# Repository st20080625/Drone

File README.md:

# 自作ドローン

## 概要
このプロジェクトは、自作ドローンの設計・製作・制御を目的としています。各種パーツの選定、組み立て、プログラムによる制御方法についてまとめています。

---

## 📝 目次

* [特徴](#-特徴)
* [外観](#-外観)
* [飛行映像](#-飛行映像)
* [操作方法](#-操作方法)
* [ハード構成](#-ハード構成)
* [インストール](#-インストール)
* [ディレクトリ構成](#-ディレクトリ構成)
* [使い方](#-使い方)
* [参考文献](#-参考文献)

---

## ✨ 特徴

* 自作のドローンファームウェア
* 拡張可能なハードウェア構成

---
## 📷️ 外観

---

## 📹️ 飛行映像
https://github.com/user-attachments/assets/ef20d2a3-a51d-4bfe-b37a-9de0bfae4551

---

## 🎮️ 操作方法
PlayStation5のコントローラを使用して飛ばすことができます。  
左スティックの上下で上昇、降下、右スティックの前後左右で前進、後退、左右移動ができます。  
R,Lボタンで向きを変更できます。  
バツボタンでセンサのキャリブレーションを行い、丸ボタンでモータの回転のオンオフができます。

---

## 🤖 ハード構成
* 制御マイコン: ESP32-WROOM-32D
* コントローラー: PlayStation5 DualSense--

* フレーム: DJI F450
* モーター: BLDC 2212 920kv * 4
* ESC: 20A (最大30A 10秒) * 4
* プロペラ: 10✕4.5 inch * 4
* バッテリー: 4S lipo 5000mAh 100C (3S lipo 2250mAh 60C程度なら満充電で1分程度飛行可能)
* ランディングギア: F450対応のもの
* LEDテープ: SK6812 * 21 (neopixel対応のものなら可) 
### 拡張用
* RaspberryPi4 4GB(RaspberryPi5 8GBはモバイルバッテリー運用は厳しい)
* モバイルバッテリー: 5V3A出力できるものなら可
* 2d lidar: rplidar a1m8

--- 
## 📦 インストール

```bash
# リポジトリをクローン
git clone https://github.com/st20080625/Drone.git

# ディレクトリに移動
cd Drone
```

---

## 📁 ディレクトリ構成

```
Drone/
├── README.md
├── images
├── include                     # ESP32フライトコントローラ用のヘッダ
├── lib                         # ps5コントローラを使うためのライブラリ
├── models                      # 3dプリンタで印刷するようのデータ
├── pcb                         # 回路図,基盤データ
├── platformio.ini              # build定義
├── recv_imu_test               # データ送信テスト
├── slam_raspi                  # マップを作るためのraspi用の環境
├── src                         # ESP32フライトコントローラの実装
```
---

## 🚀 使い方

```bash
# まずはじめにplatformioをインストールします。
pip install platformio

# 次に、src/main.cppのps5.begin(~)の~を使用するコントローラーのmacアドレスに書き換えてください。

# 次にesp32をパソコンに接続し,以下のコマンドを入力します。
# これはプロジェクトのルートディレクトリで行ってください。
platformio run --target upload

# buildとesp32に書き込みが行われます。
```

ドローンの組み立て手順や仕組みを記載します。 

ドローンの飛行を制御するには制御を行うための基盤が必要です。
kicadを使用してpcb/の中にあるdrone.kicad_proを開いて回路図とpcbを確認してください。ガーバーファイルとドリルファイルを出力し、JLCPCBなどにデータを送り、印刷してもらうか,自分でユニバーサル基板に実装するなどをして作成してください。既存ボードを刺す形式なので、使用する基盤とピン配置があっているかを確認して、異なっていれば修正してください。
基盤を固定するためにmodels/の中にあるlidar_mount.stl(追加予定)を印刷し、pcbと固定してください。
その後、f450フレームの上部プレートにネジでmount経由で固定してください。ダブルナットにすれば緩みにくくなると思います。
基盤を作成するとこのようになると思います。

これはバージョンが古いので1d lidarの配置が変わっていると思いますが、このlidarは現在は使っていないのでなくても大丈夫です。  
2dのlidarを使って環境マップを作成したい場合は印刷したmountと、pcbの穴の位置が合うように無理やり合わせ、下面にワッシャーをはさみ、lidarについている足をm2.6ネジで固定してください。

2d lidarを取り付けると次のようになると思います。  

次にf450にescとバッテリーをつなぐためのケーブルをはんだづけします。バッテリーととなぐケーブルはxt60のメス(使用するバッテリーによる)がついていればよいです。  
はんだ付けをすると次のようになります。

はんだ付けが終わったら上部のプレートに3dプリンタで作ったら上部プレートを取り付けて機体は完成です。

あとはモータとプロペラ、バッテリーを固定して最低限の飛行できる状態になります。

raspberrypiなどを乗せる説明は現状では省略します。
### 飛行原理
ドローンはプロペラを回転させることにより空気の流れを変え、揚力を生み出して浮上します。  
そのため、モータとプロペラ、回転方向の組み合わせが正しくないと飛ぶことはできません。  

              ↑ 前方
              ↑
               |
     M2(CW)       M1(CCW)
         ↻             ↺ 
           \         /
            \_______/
            /       \
         ↺              ↻
     M3(CCW)        M4(CW)
                |
                ↓ 後方
モーターは上記の回転方向になることを前提としてプログラムは書かれています。  
また、プロペラは右回転用と左回転用の２種類あり、モータの回転とあっていないと下向きに力が加わることになります。

#### 上昇

上昇する際はすべてのモータの出力を上げることで、下向きの気流が強くなり、機体に上向きの揚力が働きます。
これによりドローンは上昇します。

#### 降下

降下は上昇の逆で、すべてのモータの出力を下げることで、揚力が減少し、重力により機体がゆっくりと下降します。
モータの回転を完全に止めると急降下してしまうため、少し出力を残してバランスを取りながら降下します。

#### 前進

前方に傾くように、後方（M3・M4）のモータ出力をわずかに上げ、前方（M1・M2）の出力を下げます。
機体の推力ベクトルが前方向に傾くことで、前進運動が発生します。

       ↑ 前方
        \
         \  → 進行方向
          \
     M2(CW)       M1(CCW)
         ↻             ↺ 
           \         /
            \_______/
            /       \
         ↺              ↻
     M3(CCW)        M4(CW)

#### 後退

後退は前進の逆で、前方（M1・M2）のモータ出力を上げ、後方（M3・M4）を下げます。
これにより推力ベクトルが後ろに傾き、ドローンが後退します。

#### 左右移動

前進、後退と同様にして可能です。

#### ヨー回転（Yaw Rotation）

ドローンはプロペラの回転による**反トルク（逆方向の力）**を利用して機体を回転させます。
機体上から見たとき、モーター配置と回転方向は以下のようになっています：

              ↑ 前方
              ↑
               |
     M2(CW)         M1(CCW)
         ↻               ↺ 
           \           /
            \_________/
            /         \
         ↺               ↻
     M3(CCW)         M4(CW)
               |
               ↓ 後方

▶ 右旋回（時計回り：Yaw Right）

右に機首を向けたい場合（機体を時計回りに回したい場合）は、
CCWモータ（M1・M3）の出力を上げ、CWモータ（M2・M4）の出力を下げます。
これにより反トルクが時計回り方向に働き、機体が右に回転します。

       ↑ 前方
        \
         \  機体回転 →（右旋回：時計回り）
          \
     M2(CW)↓         ↑M1(CCW)
         ↻               ↺ 
           \           /
            \_________/
            /         \
         ↺               ↻
     M3(CCW)↑         ↓M4(CW)

◀ 左旋回（反時計回り：Yaw Left）

左に機首を向けたい場合（機体を反時計回りに回したい場合）は、
CWモータ（M2・M4）の出力を上げ、CCWモータ（M1・M3）の出力を下げます。
これにより反トルクが反時計回り方向に働き、機体が左に回転します。

       ↑ 前方
        /
       /  ← 機体回転（左旋回：反時計回り）
      /
     M2(CW)↑         ↓M1(CCW)
         ↻               ↺ 
           \           /
            \_________/
            /         \
         ↺               ↻
     M3(CCW)↓         ↑M4(CW)

このように、ドローンは4つのモータの出力バランスを変化させることで、
反トルクを利用してヨー方向の回転（機首の向き）を制御しています。

#### 制御方法
制御方法は単純でコントローラーの入力から姿勢を決定し、オイラー角表現からクォータニオン表現に変換し,imuから取得したクォータニオンとの誤差クォータニオンからトルクを取得し、PID制御で反転させて一致するようにしています。(P)  
角速度を反転させてゲイン調整して加算することで応答性を調整しています。(D)  
誤差の蓄積でドローンが滑って行くことがあるのでそれをできるだけ防ぐようにroll、pitchに対しては誤差の積分を加算して元に戻すようにしています。(I)  
地上の制御と違い地面から浮くのでPIDゲインの調整は難しかったです。  
PとDを調整するときに調整するゲイン以外を0にしてそれぞれで安定させてから、どちらも有効にして飛ばすと結構楽に飛ぶようになりました。

## 参考文献

* Emil Fresk & George Nikolakopoulos (2013). *Full Quaternion Based Attitude Control for a Quadrotor*.  
  European Control Conference (ECC), Zurich, Switzerland, July 17–19, 2013.  
  IEEE. DOI: [10.23919/ECC.2013.6669617](https://doi.org/10.23919/ECC.2013.6669617)  
  PDF（オープンアクセス）: [DiVA Portal](https://www.diva-portal.org/smash/get/diva2:1010947/FULLTEXT01.pdf)
* mebiusbox. *CGのための数学*.  
  クォータニオン章（オンライン）: [https://zenn.dev/mebiusbox/books/132b654aa02124/viewer/2966c7](https://zenn.dev/mebiusbox/books/132b654aa02124/viewer/2966c7)

---

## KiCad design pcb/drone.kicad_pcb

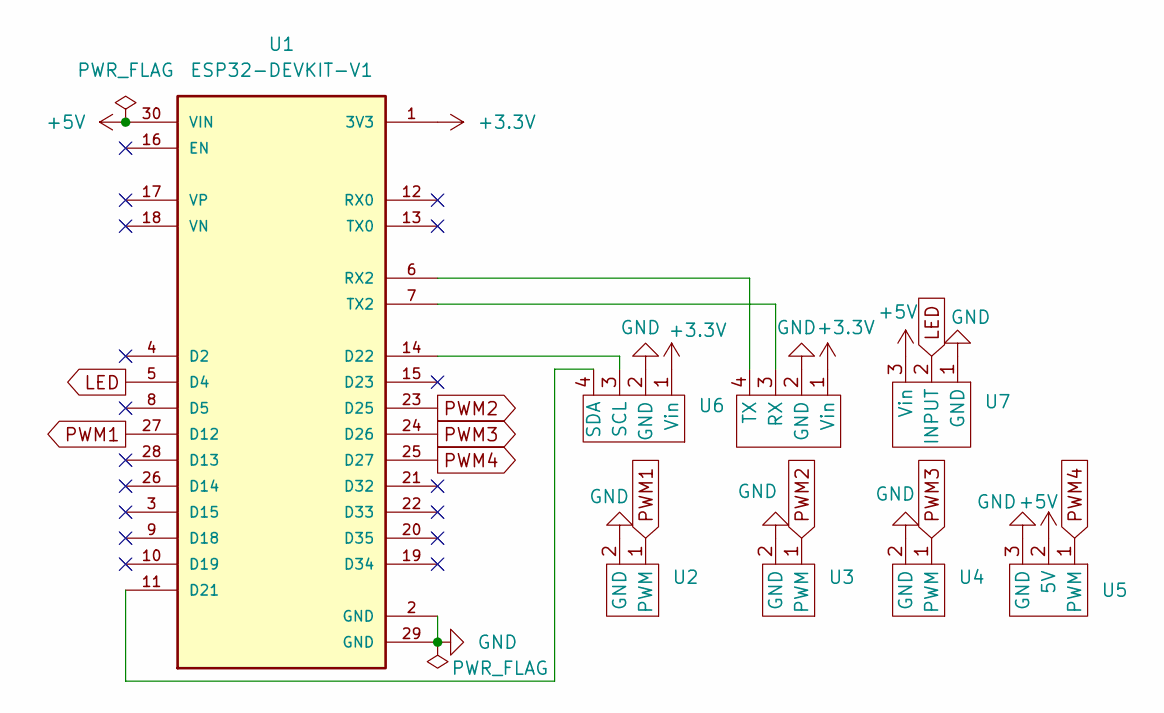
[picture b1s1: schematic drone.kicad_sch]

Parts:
L1: PinSocket_1x04_P2.54mm_Vertical
U1: ESP32-DEVKIT-V1; MODULE_ESP32_DEVKIT_V1; PARTREV N/A
U2, U3, U4: PinSocket_1x02_P2.54mm_Vertical
U5, U7: PinSocket_1x03_P2.54mm_Vertical
U6: PinSocket_1x04_P2.54mm_Vertical

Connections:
+3.3V: L1.1 (Vin), U1.1 (3V3), U6.1 (Vin)
+5V: U1.30 (VIN), U5.2 (5V), U7.3 (Vin)
GND: L1.2 (GND), U1.2 (GND), U1.29 (GND), U2.2 (GND), U3.2 (GND), U4.2 (GND), U5.3 (GND), U6.2 (GND), U7.1 (GND)
LED: U1.5 (D4), U7.2 (INPUT)
unnamed: L1.3 (RX), U1.7 (TX2)
unnamed: L1.4 (TX), U1.6 (RX2)
unnamed: U1.11 (D21), U6.4 (SDA)
unnamed: U1.14 (D22), U6.3 (SCL)
PWM1: U1.27 (D12), U2.1 (PWM)
PWM2: U1.23 (D25), U3.1 (PWM)
PWM3: U1.24 (D26), U4.1 (PWM)
PWM4: U1.25 (D27), U5.1 (PWM)

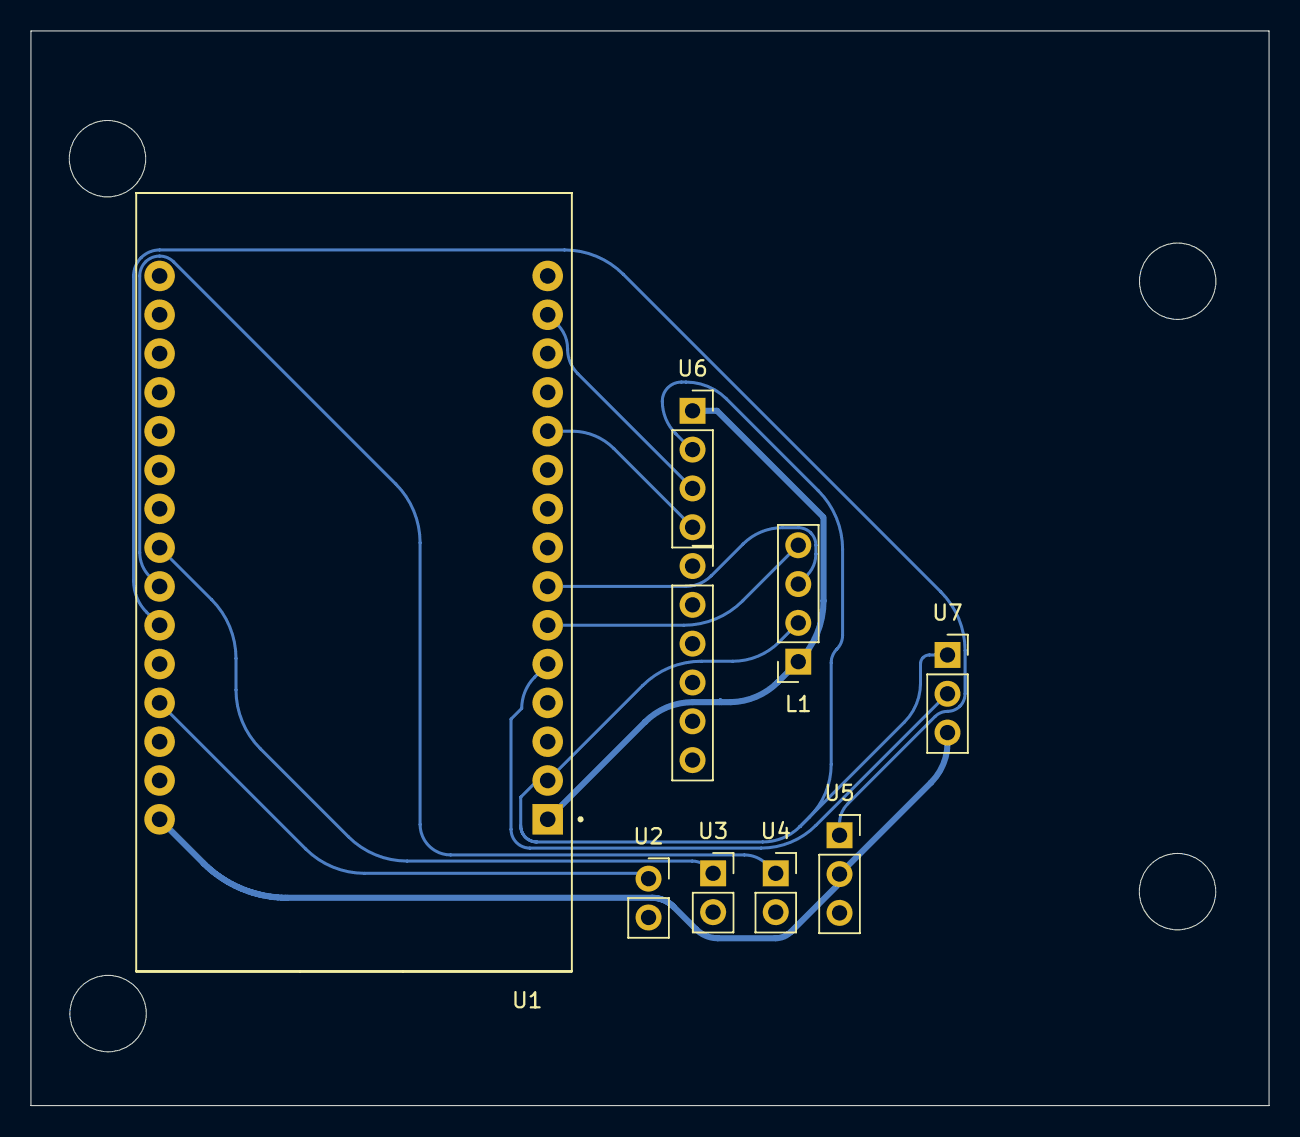
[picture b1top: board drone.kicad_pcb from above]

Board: 2 copper layers, 81.0 x 70.3 mm, 8 parts (0 on the bottom side), 12 nets.

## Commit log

2025-09-28 Yaw was Fixed but Rot was not Fixed
2025-09-28 Fixed Problems
2025-09-28 Added the Integral Controller
2025-09-29 Gain Stabled
2025-09-30 first
2025-09-30 Change CalcTarget's Roll and Pitch Range
2025-09-30 Add_Ignore
2025-09-30 Rm .Pio
2025-10-01 Add Auto_Hovering Loop
2025-10-01 Shift 50hz PWM to Oneshot125
2025-10-04 Add Hovering PID Controller
2025-10-10 Gain Tuned
2025-10-11 Flash size over
2025-10-11 Turn off the OTA
2025-10-12 Add UDP socket(just send imu data)
2025-10-14 Add send log func
2025-10-14 File Organized
2025-10-14 Fixed PCB
2025-10-23 Add Readme
2025-10-23 test
2025-10-23 Add Video
2025-10-23 Fix Readme
2025-10-24 EDIT README
